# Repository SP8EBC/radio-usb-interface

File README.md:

# An USB interface between PC/RPi/ThinClient and any Land Mobile 2way Radio
Features:
1. Single USB connection to the PC.
2. Integrated USB 2.0 hub.
3. Integrated USB audio codec IC (Texas Instruments PCM2900) detected as a regular sound card.
4. Integrated double USB-UART controller (ftdi FT2232H) to control PTT and CarrierSense/COR/ChannelBusy lines.
5. Ground Separated RS232 for communication with the radio using CAT/IV-C or simmilar protocol
6. Ground Separated audio lines
7. Spare 2 USB ports exposed from the hub for connecting external devices.

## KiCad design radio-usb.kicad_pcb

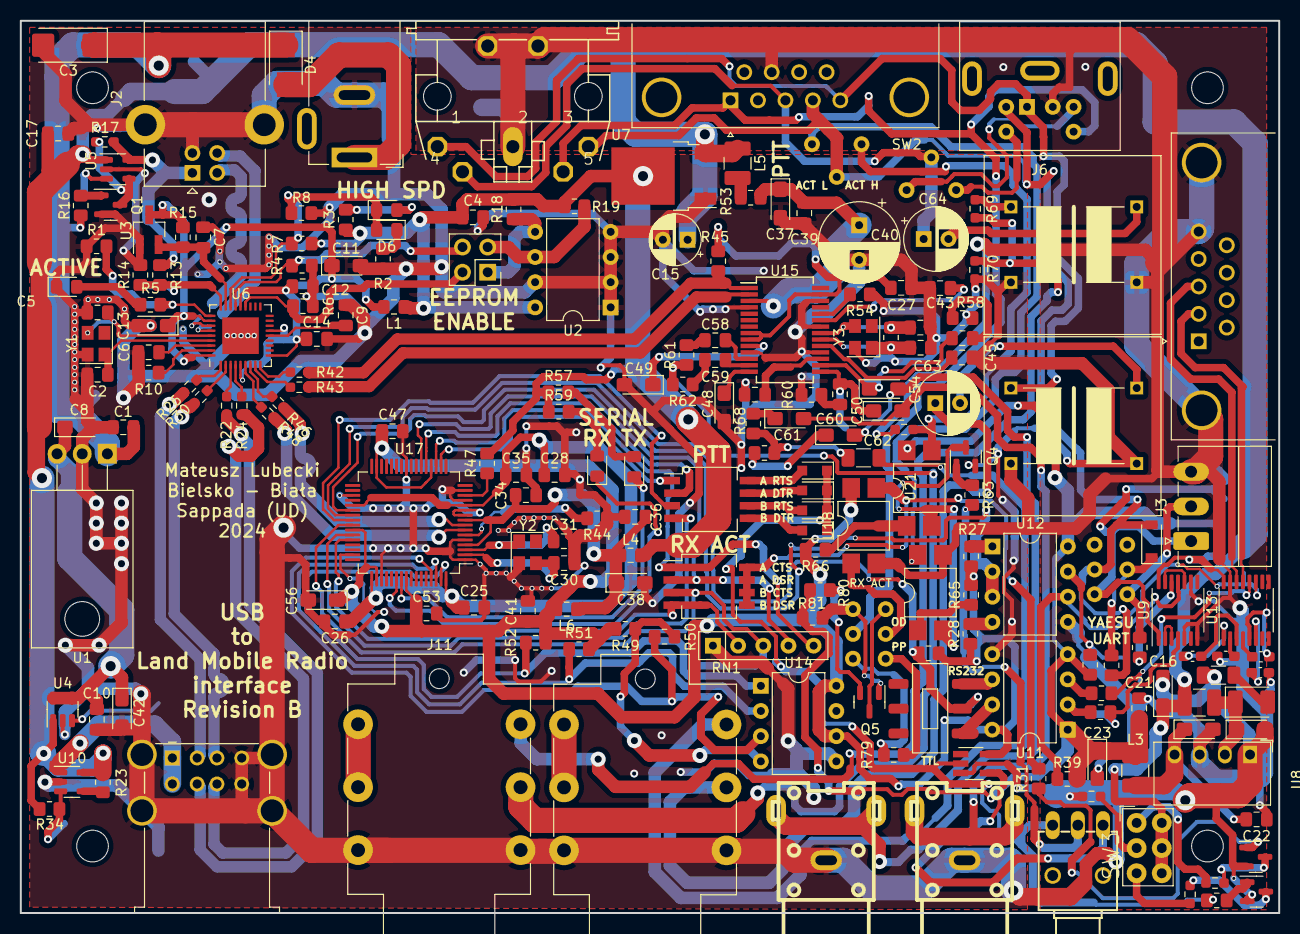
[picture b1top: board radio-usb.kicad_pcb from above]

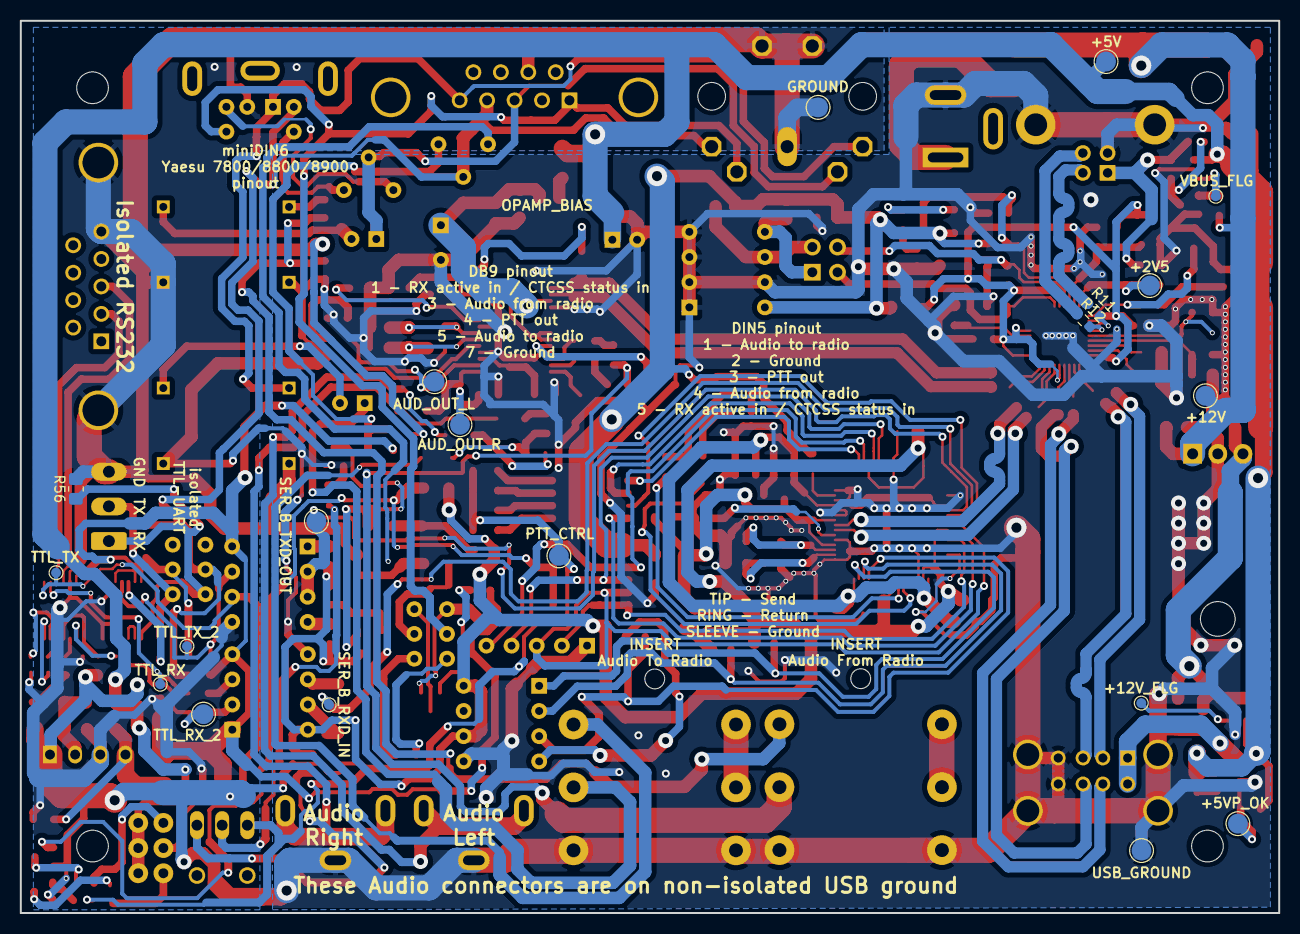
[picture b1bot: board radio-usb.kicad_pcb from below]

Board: 2 copper layers, 127.0 x 90.0 mm, 225 parts (20 on the bottom side), 171 nets.

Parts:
C1, C4, C7, C10, C12, C14, C17, C21, C22, C25, C26, C34, C35, C36, C39, C41, C47, C53: 100n; C_0805_2012Metric_Pad1.18x1.45mm_HandSolder
C2, C5, C30, C31, C51, C52: 18p; C_0805_2012Metric_Pad1.18x1.45mm_HandSolder
C3: 10u; CP_EIA-6032-28_Kemet-C_Pad2.25x2.35mm_HandSolder
C6, C9, C27, C43, C45, C46: 1u; C_0805_2012Metric_Pad1.18x1.45mm_HandSolder
C8, C11, C13, C37, C38, C48, C49, C50, C54, C56, C60, C61: 10u; CP_EIA-3216-18_Kemet-A_Pad1.58x1.35mm_HandSolder
C15: 100u; CP_Radial_D5.0mm_P2.50mm
C16, C18, C20, C23, C42: 22u; CP_EIA-3216-18_Kemet-A_Pad1.58x1.35mm_HandSolder
C19: 100u; CP_EIA-3528-21_Kemet-B_Pad1.50x2.35mm_HandSolder
C24, C29, C32, C33: 100n; C_0603_1608Metric_Pad1.08x0.95mm_HandSolder
C28: 3u3; C_0805_2012Metric_Pad1.18x1.45mm_HandSolder
C40: 470u; CP_Radial_D8.0mm_P3.50mm
C55, C57: 22n; C_0805_2012Metric_Pad1.18x1.45mm_HandSolder
C58, C59: 4u7; C_0805_2012Metric_Pad1.18x1.45mm_HandSolder
C62: 10u; C_1206_3216Metric_Pad1.33x1.80mm_HandSolder
C63, C64: 220u; CP_Radial_D6.3mm_P2.50mm
D1: LED_ACTIVE; LED_0805_2012Metric_Pad1.15x1.40mm_HandSolder
D4: B130-13-F; D_SMA
D5: DNP; LED_0805_2012Metric_Pad1.15x1.40mm_HandSolder
D6: LED_HS; LED_0805_2012Metric_Pad1.15x1.40mm_HandSolder
D7: 1N4148W; D_SOD-123
D12: 1882.2781; LED_MENTOR_1882
D15, D16: LED; LED_0805_2012Metric_Pad1.15x1.40mm_HandSolder
D17, D18, D19, D20: RB751V40T1G; D_SOD-323_HandSoldering
H1, H2, H3, H4: MountingHole; MountingHole_3.2mm_M3
J1: Barrel_Jack; BarrelJack_GCT_DCJ200-10-A_Horizontal
J2: miniUSB; USB_B_Lumberg_2411_02_Horizontal
J3: 15EDGRC-3.5-03P-14; PhoenixContact_MC_1,5_3-G-3.5_1x03_P3.50mm_Horizontal
J4: DB9_Female; DSUB-9_Female_Horizontal_P2.77x2.84mm_EdgePinOffset4.94mm_H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
J5: EEP_EN; PinHeader_2x02_P2.54mm_Vertical
J6: Mini-DIN-6; Mini-DIN_Female_TM0508A
J7: EDAC 690-008-221-904; USB_A_Wuerth_61400826021_Horizontal_Stacked
J8: DB9_Male; DSUB-9_Male_Horizontal_P2.77x2.84mm_EdgePinOffset4.94mm_Hou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
J9, J10: Conn_Coaxial; rca_cliff_F68371
J11, J12: ACJS-MHDRM; Jack_6.35mm_ACJS-MHDRM
L1, L4, L6: 1u; L_0805_2012Metric_Pad1.15x1.40mm_HandSolder
L2, L3, L5: 4u7; L_1210_3225Metric_Pad1.42x2.65mm_HandSolder
Q1, Q2, Q3, Q4: BC846C; SOT-23
Q5: BC856; SOT-23
R1, R3, R7: DNP; R_0805_2012Metric_Pad1.20x1.40mm_HandSolder
R2, R5, R57, R59: 620; R_0805_2012Metric_Pad1.20x1.40mm_HandSolder
R4, R6, R8, R13, R14, R15: 100k; R_0805_2012Metric_Pad1.20x1.40mm_HandSolder
R9: 4k7; R_0805_2012Metric_Pad1.20x1.40mm_HandSolder
R10, R44: 12k; R_0805_2012Metric_Pad1.20x1.40mm_HandSolder
R11, R12, R42, R43, R46, R48: 22; R_0603_1608Metric_Pad0.98x0.95mm_HandSolder
R16, R18, R19, R23, R38, R39, R49, R51, R52, R61, R62, R67, R68: 10k; R_0805_2012Metric_Pad1.20x1.40mm_HandSolder
R17, R78: 10k; R_0603_1608Metric_Pad0.98x0.95mm_HandSolder
R20: 0R68; R_1206_3216Metric_Pad1.30x1.75mm_HandSolder
R22, R24, R26, R30: 33; R_0603_1608Metric_Pad0.98x0.95mm_HandSolder
R27, R28, R32, R33, R79, R80: 680; R_0805_2012Metric_Pad1.20x1.40mm_HandSolder
R29, R31, R40, R41, R50, R56, R63: 2k2; R_0805_2012Metric_Pad1.20x1.40mm_HandSolder
R34: R_Small; R_0805_2012Metric_Pad1.20x1.40mm_HandSolder
R35, R36, R37: 620; R_0603_1608Metric_Pad0.98x0.95mm_HandSolder
R45: 1k5; R_0805_2012Metric_Pad1.20x1.40mm_HandSolder
R47: 1k; R_0805_2012Metric_Pad1.20x1.40mm_HandSolder
R53: 2R2; R_0805_2012Metric_Pad1.20x1.40mm_HandSolder
R54: 0; R_0805_2012Metric_Pad1.20x1.40mm_HandSolder
R55: 1M; R_0805_2012Metric_Pad1.20x1.40mm_HandSolder
R58, R60: 16R; R_0805_2012Metric_Pad1.20x1.40mm_HandSolder
R65, R66: 330; R_0805_2012Metric_Pad1.20x1.40mm_HandSolder
R69: 0; R_0603_1608Metric_Pad0.98x0.95mm_HandSolder
R70: DNP; R_0603_1608Metric_Pad0.98x0.95mm_HandSolder
R81: 22k; R_0805_2012Metric_Pad1.20x1.40mm_HandSolder
RN1: 10k; R_Array_SIP5
SW1: SW_Push_DPDT; Alps_SSSS222700
SW2, SW7: SW_SPDT; Alps_SSSS213000
SW3: SW_SPDT; TL3XWO
SW4, SW5: A6H-4101; SW_DIP_SPSTx04_Slide_Copal_CHS-04B_W7.62mm_P1.27mm
SW6: SW_DPDT_x2; Alps_SSSS222700
SW8: SW_SPDT; Ninigi_MSS-2235S
TP1: +12V_FLG; TestPoint_Pad_D1.0mm
TP2: VB_FLG; TestPoint_Pad_D1.0mm
TP3: +5VP_OK; TestPoint_Pad_D2.0mm
TP4: TTL_TX; TestPoint_Pad_D1.0mm
TP5: TTL_RX; TestPoint_Pad_D1.0mm
TP6: TTL_TX_2; TestPoint_Pad_D1.0mm
TP7: TTL_RX_2; TestPoint_Pad_D2.0mm
TP8: SER_B_TXD_OUT; TestPoint_Pad_D2.0mm
TP9: SER_B_RXD_IN; TestPoint_Pad_D1.0mm
TP10: AUD_OUT_L; TestPoint_Pad_D2.0mm
TP11: AUD_OUT_R; TestPoint_Pad_D2.0mm
TP13: PTT_CTRL; TestPoint_Pad_D2.0mm
TP14: USB_GROUND; TestPoint_Pad_D2.0mm
TP15: GROUND; TestPoint_Pad_D2.0mm
TP16: +12V; TestPoint_Pad_D2.0mm
TP17: +2V5; TestPoint_Pad_D2.0mm
TP18: +5V; TestPoint_Pad_D2.0mm
U1: L7805; TO-220-3_Horizontal_TabDown
U2: 24LC04; DIP-8_W7.62mm
U3: APX809_810-xxSA; SOT-23_Handsoldering
U4, U5: AP22814AW5; SOT-23-5
U6: USB2514B-AEZC; QFN-36-1EP_6x6mm_P0.5mm_EP3.7x3.7mm
U7: LM1117-3.3; TO-252-2
U8: TBA 1-0511; Converter_DCDC_Murata_CRE1xxxxxx3C_THT
U9: 4069; TSSOP-14_4.4x5mm_P0.65mm
U10: AP2171W; SOT-23-5
U11, U12: TLP2662; DIP-8_W7.62mm
U13: MAX3232; TSSOP-16_4.4x5mm_P0.65mm
U14: AT93C46D; DIP-8_W7.62mm
U15: PCM2900CDB; SSOP-28_5.3x10.2mm_P0.65mm
U16: 74AHCT1G04; SOT-23-5_HandSoldering
U17: FT2232HL; LQFP-64_10x10mm_P0.5mm
U18, U20, U21: PC817; SMDIP-4_W7.62mm
U19, U22: CRIYCHLEY9000; NORMAL
X1: MAB5SH
Y1: 24MHz; Crystal_SMD_Abracon_ABM8G-4Pin_3.2x2.5mm
Y2, Y3: 12MHz; Crystal_SMD_Abracon_ABM8G-4Pin_3.2x2.5mm

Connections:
+1V8: C25.1, C26.1, C28.1, C35.1, U17.12 (VCORE), U17.37 (VCORE), U17.49 (VREGOUT), U17.64 (VCORE)
+2V5: R13.2, R14.1, TP17.1, U6.27 (VBUS_DET)
+3V3: C4.1, L1.1, L4.1, R3.1, R7.1, R18.2, R19.2, R47.2, R57.1, R59.1, U2.8 (VCC), U7.2 (VO)
+5V: C15.1, C16.1, C17.1, D12.1 (AB), D12.3 (AR), D12.5 (AG), L2.1, L5.1, R23.2, R34.1, TP18.1, U4.1 (OUT), U5.1 (OUT), U7.3 (VI), U10.5 (IN)
+5VP: J7.1 (VBUS1), J7.5 (VBUS2), U10.1 (OUT)
+12V: C1.1, C3.1, D4.1 (K), R16.1, TP16.1, U1.1 (IN)
/5VD12: C8.1, C10.1, C42.1, U1.3 (OUT), U4.4 (EN), U4.5 (IN)
/+5VP_EN: R23.1, U10.4 (EN)
/+5VP_OK: R34.2, TP3.1, U10.3 (~FLG)
/AF_FRM_RADIO_PREINS: J11.T, R69.1, R70.2
/AUD_IN_LEFT: C58.1, U15.12 (VINL)
/AUD_IN_RIGHT: C59.1, U15.13 (VINR)
/AUD_IN_SUM: J11.R, R61.1, R62.2
/AUD_OUT_LEFT: C54.1, C55.2, TP10.1, U15.16 (VOUTL)
/AUD_OUT_RIGHT: C50.1, C57.2, TP11.1, U15.15 (VOUTR)
/AUD_OUT_SUM: C62.2, J12.T
/AUD_USB_DN: R43.2, U15.2 (D-)
/AUD_USB_DP: R42.2, R45.1, U15.1 (D+)
/AUD_VBUS: C37.1, C39.1, C40.1, R53.2, U15.3 (VBUS)
/AUD_VDDI: C27.1, R45.2, U15.8 (SEL0), U15.9 (SEL1), U15.27 (VDDI)
/CAT_UART_RX: J3.1, R56.1, SW1.6 (C), U9.1
/CAT_UART_TX: J3.2, R40.1, SW1.3 (C)
/D+: J2.3 (D+), R12.1
/D-: J2.2 (D-), R11.1
/DCDC_IN: C18.1, C19.1, L2.2, U8.2 (+VIN)
/DCDC_OUT: C20.1, C22.2, L3.1, U8.4 (+VOUT)
/DP1+: J7.3 (D1+), R30.2
/DP1-: J7.2 (D1-), R26.2
/DP2+: J7.7 (D2+), R24.2
/DP2-: J7.6 (D2-), R22.2
/H_AUD_USBD+: R42.1, U6.9 (USBDP_DN4/PRT_DIS_P4)
/H_AUD_USBD-: R43.1, U6.8 (USBDM_DN4/PRT_DIS_M4)
/H_BIAS: R10.2, U6.35 (RBIAS)
/H_DP1+: R30.1, U6.2 (USBDP_DN1/PRT_DIS_P1)
/H_DP1-: R26.1, U6.1 (USBDM_DN1/PRT_DIS_M1)
/H_DP2+: R24.1, U6.4 (USBDP_DN2/PRT_DIS_P2)
/H_DP2-: R22.1, U6.3 (USBDM_DN2/PRT_DIS_M2)
/H_EE_SCL: J5.3, R19.1, U2.6 (SCL)
/H_EE_SDA: J5.1, R18.1, U2.5 (SDA)
/H_HOST_USBD+: R12.2, U6.31 (USBDP_UP)
/H_HOST_USBD-: R11.2, U6.30 (USBDM_UP)
/H_REM0: R1.2, R5.2, U6.28 (SUSP_IND/LOCAL_PWR/NON_REM0)
/H_REM1: J5.2, R6.2, U6.22 (SDA/SMBDATA/NON_REM1)
/H_RST: C7.2, R15.2, U3.2 (~RST), U6.26 (RESET_N)
/H_SEL0: J5.4, R4.2, U6.24 (SCL/SMBCLK/CFG_SEL0)
/H_SEL1: D5.1 (K), D6.2 (A), R7.2, R8.2, U6.25 (HS_IND/CFG_SEL1)
/H_SER_USBD+: R46.1, U6.7 (USBDP_DN3/PRT_DIS_P3)
/H_SER_USBD-: R48.1, U6.6 (USBDM_DN3/PRT_DIS_M3)
/H_VDD: C11.1, C12.1, C13.1, C14.1, L1.2, R15.1, U3.3 (Vcc), U6.5 (VDDA33), U6.10 (VDDA33), U6.15 (VDD33), U6.23 (VDD33), U6.29 (VDDA33), U6.36 (VDDA33)
/H_XTALIN: C2.1, U6.33 (XTALIN/CLKIN), Y1.1
/H_XTALO: C5.1, U6.32 (XTALOUT), Y1.3
/PTT_ACTH: R78.1, SW7.3 (C), U21.3
/PTT_ACTL: SW7.1 (A), U20.4
/PTT_CTRL: D17.1 (K), D18.1 (K), D19.1 (K), D20.1 (K), R41.2, SW3.3 (C), TP13.1, U16.2
/PTT_CTRL_SW: Q4.1 (B), R63.1
/RCA_LEFT: C54.2, C60.2, J10.1 (In)
/RCA_RIGHT: C50.2, C61.2, J9.1 (In)
/RS232RX: J8.2, U13.13 (R1IN)
/RS232TX: J8.3, U13.14 (T1OUT)
/RX_ACT_SEP: R31.2, SW5.5, SW5.6, SW5.7, SW5.8, U18.3
/SER_A_CTS_IN: RN1.5 (R4), SW5.1, U17.19 (ADBUS3)
/SER_A_DSR_IN: RN1.4 (R3), SW5.2, U17.22 (ADBUS5)
/SER_A_DTR_OUT: SW4.2, U17.21 (ADBUS4)
/SER_A_RTS_OUT: SW4.1, U17.18 (ADBUS2)
/SER_B_CTS_IN: RN1.3 (R2), SW5.3, U17.41 (BDBUS3)
/SER_B_DSR_IN: RN1.2 (R1), SW5.4, U17.44 (BDBUS5)
/SER_B_DTR_OUT: SW4.4, U17.43 (BDBUS4)
/SER_B_RTS_OUT: SW4.3, U17.40 (BDBUS2)
/SER_B_RXD_IN: R29.1, SW8.2 (B), TP9.1, U17.39 (BDBUS1)
/SER_B_RXD_RS: SW8.3 (C), U11.6 (VO2)
/SER_B_RXD_TTL: SW8.1 (A), U11.7 (VO1)
/SER_B_RXLED: D16.1 (K), U17.54 (BCBUS3)
/SER_B_TXD_OUT: TP8.1, U12.2 (C1), U12.3 (C2), U17.38 (BDBUS0)
/SER_B_TXLED: D15.1 (K), U17.55 (BCBUS4)
/SER_D+: R46.2, U17.8 (DP)
/SER_D-: R48.2, U17.7 (DM)
/SER_EECS: R52.1, U14.1 (CS), U17.63 (EECS)
/SER_EEDT: R50.1, U14.3 (DI), U17.61 (EEDATA)
/SER_VPLL: C34.1, C36.1, C38.1, L4.2, L6.1, U17.4 (VPHY), U17.9 (VPLL)
/SER_XI: C30.1, U17.2 (OSCI), Y2.3
/SER_XO: C31.1, U17.3 (OSCO), Y2.1
/TTL_RX: R33.2, TP5.1, U13.12 (R1OUT)
/TTL_RX_2: R32.2, TP7.1, U9.4
/TTL_TX: R39.1, TP4.1, U12.6 (VO2), U13.11 (T1IN)
/TTL_TX_2: R38.1, TP6.1, U9.11, U12.7 (VO1)
/YAESU_FILTERED_AUD: J6.5, SW2.1 (A)
/YAESU_FLAT_AUD: J6.4, SW2.3 (C)
/~PTT_CTRL: SW3.1 (A), U16.4
/~SER_RST: R47.1, U17.14 (~RESET)
AF_FRM_RADIO: C64.1, J4.3, SW2.2 (B), X1.4
AF_TO_RADIO: J4.5, J6.1, U19.P$1, X1.1
GND: C1.2, C2.2, C3.2, C4.2, C5.2, C6.1, C7.1, C8.2, C9.1, C10.2, C11.2, C12.2, C13.2, C14.2, C15.2, C16.2, C17.2, C18.2, C25.2, C26.2, C27.2, C28.2, C30.2, C31.2, C34.2, C35.2, C36.2, C37.2, C38.2, C39.2, C40.2, C41.2, C42.2, C43.2, C45.2, C46.2, C47.2, C48.2, C49.2, C51.2, C52.2, C53.2, C56.2, D1.1 (K), J1.2, J2.4 (GND), J2.5 (Shield), J7.4 (GND1), J7.8 (GND2), J7.9 (Shield), J9.2 (Ext), J10.2 (Ext), J11.S, J11.SN, J12.S, J12.SN, Q1.2 (E), Q2.2 (E), Q3.2 (E), Q4.2 (E), R1.1, R2.1, R4.1, R6.1, R8.1, R10.1, R14.2, R20.1, R35.2, R44.1, R54.1, R58.1, R60.1, R70.1, RN1.1 (common), TP14.1, U1.2 (GND), U2.1 (A0), U2.2 (A1), U2.3 (A2), U2.4 (GND), U2.7 (WP), U3.1 (GND), U4.2 (GND), U5.2 (GND), U6.37 (VSS), U7.1 (GND), U8.1 (-VIN), U10.2 (GND), U11.5 (GND), U14.5 (GND), U15.4 (DGNDU), U15.11 (AGNDC), U15.18 (AGNDP), U15.22 (AGNDX), U15.26 (DGND), U16.3 (GND), U17.1 (GND), U17.5 (GND), U17.10 (AGND), U17.11 (GND), U17.13 (TEST), U17.15 (GND), U17.25 (GND), U17.35 (GND), U17.47 (GND), U17.51 (GND), U19.P$4, U22.P$2, Y1.4, Y2.2, Y3.4
GNDREF: C20.2, C21.2, C22.1, C23.2, C32.2, C33.2, J3.3, J4.7, J6.2, J8.0 (PAD), J8.5, R56.2, R78.2, TP15.1, U8.3 (-VOUT), U9.5, U9.7 (VSS), U9.9, U12.5 (GND), U13.15 (GND), U18.2, U19.P$2, U20.3, U22.P$4, X1.2, X1.PE, X1.PE@ (PE)
unnamed: C6.2, U6.34 (PLLFILT)
unnamed: C9.2, U6.14 (CRFILT)
unnamed: C19.2, R20.2
unnamed: C24.1, U13.1 (C1+)
unnamed: C24.2, U13.3 (C1-)
unnamed: C29.1, U13.4 (C2+)
unnamed: C29.2, U13.5 (C2-)
unnamed: C32.1, U13.2 (VS+)
unnamed: C33.1, U13.6 (VS-)
unnamed: C43.1, U15.23 (VCCXI)
unnamed: C45.1, U15.19 (VCCP2I)
unnamed: C46.1, U15.17 (VCCP1I)
unnamed: C48.1, U15.14 (VCOM)
unnamed: C49.1, U15.10 (VCCCI)
unnamed: C51.1, R55.2, U15.21 (XTI), Y3.3
unnamed: C52.1, R55.1, U15.20 (XTO), Y3.1
unnamed: C55.1, R58.2
unnamed: C57.1, R60.2
unnamed: C58.2, R61.2
unnamed: C59.2, R62.1
unnamed: C60.1, R67.1
unnamed: C61.1, R68.1
unnamed: C62.1, R67.2, R68.2
unnamed: C63.1, J12.R
unnamed: C63.2, U19.P$3
unnamed: C64.2, U22.P$3
unnamed: D1.2 (A), R5.1
unnamed: D4.2 (A), J1.1
unnamed: D5.2 (A), R3.2
unnamed: D6.1 (K), R2.2
unnamed: D7.1 (K), R9.1, SW1.2 (B)
unnamed: D12.2 (KB), R37.1
unnamed: D12.4 (KR), R35.1
unnamed: D12.6 (KR), R36.1
unnamed: D15.2 (A), R57.2
unnamed: D16.2 (A), R59.2
unnamed: D17.2 (A), SW4.8
unnamed: D18.2 (A), SW4.7
unnamed: D19.2 (A), SW4.6
unnamed: D20.2 (A), SW4.5
unnamed: J11.RN, J11.TN
unnamed: J12.RN, J12.TN
unnamed: L5.2, R53.1
unnamed: Q1.1 (B), R16.2
unnamed: Q1.3 (C), R17.1, U5.4 (EN)
unnamed: Q2.1 (B), R31.1
unnamed: Q2.3 (C), R37.2
unnamed: Q3.1 (B), R41.1
unnamed: Q3.3 (C), R36.2
unnamed: Q4.3 (C), U20.2, U21.2
unnamed: Q5.1 (B), R81.1, SW6.4 (A)
unnamed: Q5.2 (E), R80.1
unnamed: Q5.3 (C), SW6.1 (A)
unnamed: R27.2, U12.1 (A1)
unnamed: R28.2, U12.4 (A2)
unnamed: R32.1, U11.2 (C1)
unnamed: R33.1, U11.3 (C2)
unnamed: R40.2, U9.12
unnamed: R44.2, U17.6 (REF)
unnamed: R49.1, R50.2, U14.4 (DO)
unnamed: R51.1, U14.2 (SCLK), U17.62 (EECLK)
unnamed: R54.2, U15.24 (DIN)
unnamed: R63.2, SW3.2 (B)
unnamed: R65.1, U20.1
unnamed: R66.1, U21.1
unnamed: R69.2, U22.P$1
unnamed: R79.1, SW6.6 (C)
unnamed: R79.2, SW6.3 (C)
unnamed: SW6.2 (B), U18.1
unnamed: TP1.1, U4.3 (~FLG)
unnamed: TP2.1, U5.3 (~FLG)
unnamed: U9.2, U9.3
unnamed: U9.10, U9.13
PTT: D7.2 (A), J4.4, J6.3, R9.2, SW1.5 (B), SW7.2 (B), X1.3
RX_ACTIVE: J4.1, J6.6, SW6.5 (B), X1.5
VBUS: J2.1 (VBUS), R13.1, R17.2, U5.5 (IN)
VCC: C41.1, C47.1, C53.1, C56.1, L6.2, R27.1, R28.1, R29.2, R49.2, R51.2, R52.2, R65.2, R66.2, U11.8 (VCC), U14.6 (ORG), U14.8 (VCC), U16.5 (VCC), U17.20 (VCCIO), U17.31 (VCCIO), U17.42 (VCCIO), U17.50 (VREGIN), U17.56 (VCCIO), U18.4
VD: C21.1, C23.1, L3.2, R38.2, R39.2, R80.2, R81.2, U9.14 (VDD), U11.1 (A1), U11.4 (A2), U12.8 (VCC), U13.16 (VCC), U21.4

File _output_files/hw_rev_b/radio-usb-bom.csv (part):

Reference, Quantity, Value, Footprint, Datasheet, DESCRIPTION
C1 C4 C7 C10 C12 C14 C17 C21 C22 C25 C26 C34 C35 C36 C39 C41 C47 C53 ,18,"100n","Capacitor_SMD:C_0805_2012Metric_Pad1.18x1.45mm_HandSolder","","08051C104KAT2A KYOCERA AVX"
C15 ,1,"100u","Capacitor_THT:CP_Radial_D5.0mm_P2.50mm","https://www.tme.eu/Document/4bbe885c35326128adf3c0aebd83337c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","UBT1H101MPD8 NICHICON"
C16 C18 C20 C23 C42 ,5,"22u","Capacitor_Tantalum_SMD:CP_EIA-3216-18_Kemet-A_Pad1.58x1.35mm_HandSolder","","TPSA106K010R0900 KYOCERA AVX"
C19 ,1,"100u","Capacitor_Tantalum_SMD:CP_EIA-3528-21_Kemet-B_Pad1.50x2.35mm_HandSolder","","TPSA106K010R0900 KYOCERA AVX"
C2 C5 C30 C31 C51 C52 ,6,"18p","Capacitor_SMD:C_0805_2012Metric_Pad1.18x1.45mm_HandSolder","","08055A180JAT2A KYOCERA AVX"
C24 C29 C32 C33 ,4,"100n","Capacitor_SMD:C_0603_1608Metric_Pad1.08x0.95mm_HandSolder","","06033G104ZAT2A KYOCERA AVX"
C28 ,1,"3u3","Capacitor_SMD:C_0805_2012Metric_Pad1.18x1.45mm_HandSolder","","0805ZD335KAT2A KYOCERA AVX"
C3 ,1,"10u","Capacitor_Tantalum_SMD:CP_EIA-6032-28_Kemet-C_Pad2.25x2.35mm_HandSolder","","TPSA106K010R0900 KYOCERA AVX"
C40 ,1,"470u","Capacitor_THT:CP_Radial_D8.0mm_P3.50mm","","NICHICON UHE1A471MPD1TA "
C55 C57 ,2,"22n","Capacitor_SMD:C_0805_2012Metric_Pad1.18x1.45mm_HandSolder","","08051C223KAT2A KYOCERA AVX"
C58 C59 ,2,"4u7","Capacitor_SMD:C_0805_2012Metric_Pad1.18x1.45mm_HandSolder","","0805YC475KAT2A KYOCERA AVX"
C6 C9 C27 C43 C45 C46 ,6,"1u","Capacitor_SMD:C_0805_2012Metric_Pad1.18x1.45mm_HandSolder","","0805YC105KAT2A KYOCERA AVX"
C62 ,1,"10u","Capacitor_SMD:C_1206_3216Metric_Pad1.33x1.80mm_HandSolder","","CL31A106MAHNNNE SAMSUNG"
C63 C64 ,2,"220u","Capacitor_THT:CP_Radial_D6.3mm_P2.50mm","https://www.tme.eu/Document/4bbe885c35326128adf3c0aebd83337c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","EEUFR1C221 PANASONIC"
C8 C11 C13 C37 C38 C48 C49 C50 C54 C56 C60 C61 ,12,"10u","Capacitor_Tantalum_SMD:CP_EIA-3216-18_Kemet-A_Pad1.58x1.35mm_HandSolder","","TPSA106K010R0900 KYOCERA AVX"
D1 ,1,"LED_ACTIVE","LED_SMD:LED_0805_2012Metric_Pad1.15x1.40mm_HandSolder","","KPT-2012CGCK KINGBRIGHT ELECTRONIC"
D12 ,1,"1882.2781","LED:LED_MENTOR_1882","https://www.cree.com/led-components/media/documents/1397-QLS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","1882.2781 MENTOR"
D15 D16 ,2,"LED","LED_SMD:LED_0805_2012Metric_Pad1.15x1.40mm_HandSolder","","KP-2012SYCK KINGBRIGHT ELECTRONIC"
D17 D18 D19 D20 ,4,"RB751V40T1G","Diode_SMD:D_SOD-323_HandSoldering","https://www.tme.eu/Document/b77eb958f5d9ac56ef472a800d34775b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","RB751V40T1G ONSEMI"
D4 ,1,"B130-13-F","Diode_SMD:D_SMA","","B130-13-F DIODES INCORPORATED"
D5 D6 ,2,"LED_HS","LED_SMD:LED_0805_2012Metric_Pad1.15x1.40mm_HandSolder","","KPT-2012SURC KINGBRIGHT ELECTRONIC"
D7 ,1,"1N4148W","Diode_SMD:D_SOD-123","https://www.vishay.com/docs/85748/1n4148w.pdf","1N4148W-AQ DIOTEC SEMICONDUCTOR"
H1 H2 H3 H4 ,4,"MountingHole","MountingHole:MountingHole_3.2mm_M3",""
J1 ,1,"Barrel_Jack","Connector_BarrelJack:BarrelJack_GCT_DCJ200-10-A_Horizontal",""
J11 J12 ,2,"ACJS-MHDRM","AV:Jack_6.35mm_ACJS-MHDRM","","ACJS-MHDRM AMPHENOL"
J2 ,1,"miniUSB","Connector_USB:USB_B_Lumberg_2411_02_Horizontal"," ~","DS1099-WN0 CONNFLY"
J3 ,1,"15EDGRC-3.5-03P-14","Connector_Phoenix_MC:PhoenixContact_MC_1,5_3-G-3.5_1x03_P3.50mm_Horizontal","https://www.tme.eu/Document/c7e2facf434c6541c93efde757aaf5e6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"
J4 ,1,"DB9_Female","Connector_Dsub:DSUB-9_Female_Horizontal_P2.77x2.84mm_EdgePinOffset4.94mm_Housed_MountingHolesOffset7.48mm"," ~","DE09-SN-24 ADAM TECH"
J5 ,1,"EEP_EN","Connector_PinHeader_2.54mm:PinHeader_2x02_P2.54mm_Vertical",""
J6 ,1,"Mini-DIN-6","AV:Mini-DIN_Female_TM0508A","http://service.powerdynamics.com/ec/Catalog17/Section%2011.pdf","4850.2610 SCHURTER"
J7 ,1,"EDAC 690-008-221-904","Connector_USB:USB_A_Wuerth_61400826021_Horizontal_Stacked","https://www.tme.eu/Document/bc38f05e107515c145d033d39722883f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","EDAC 690-008-221-904"
J8 ,1,"DB9_Male","Connector_Dsub:DSUB-9_Male_Horizontal_P2.77x2.84mm_EdgePinOffset4.94mm_Housed_MountingHolesOffset7.48mm"," ~","DE09-PN-24 ADAM TECH"
J9 J10 ,2,"Conn_Coaxial","AV:rca_cliff_F68371"," ~"
L1 L4 L6 ,3,"1u","Inductor_SMD:L_0805_2012Metric_Pad1.15x1.40mm_HandSolder","","Viking NL05KTC1R0 "
L2 L3 L5 ,3,"4u7","Inductor_SMD:L_1210_3225Metric_Pad1.42x2.65mm_HandSolder","https://www.tme.eu/Document/11b7ed33a7ee93321756e8b8c8bd2191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","Viking NLV10MTC4R7"
Q1 Q2 Q3 Q4 ,4,"BC846C","Package_TO_SOT_SMD:SOT-23","https://assets.nexperia.com/documents/data-sheet/BC846_SER.pdf","BC846C-AQ DIOTEC SEMICONDUCTOR"
Q5 ,1,"BC856","Package_TO_SOT_SMD:SOT-23","https://www.onsemi.com/pub/Collateral/BC860-D.pdf","BC856B-AQ DIOTEC SEMICONDUCTOR"
R1 R4 R6 R8 R13 R14 R15 ,7,"100k","Resistor_SMD:R_0805_2012Metric_Pad1.20x1.40mm_HandSolder","","ERJ6ENF1002V PANASONIC"
R10 R44 ,2,"12k","Resistor_SMD:R_0805_2012Metric_Pad1.20x1.40mm_HandSolder","","ERJ6ENF1202V PANASONIC"
R11 R12 R42 R43 R46 R48 ,6,"22","Resistor_SMD:R_0603_1608Metric_Pad0.98x0.95mm_HandSolder","","ERJ3EKF22R0V PANASONIC"
R17 R78 ,2,"10k","Resistor_SMD:R_0603_1608Metric_Pad0.98x0.95mm_HandSolder","","ERJ3EKF1002V PANASONIC"
R2 R3 R5 R57 R59 ,5,"620","Resistor_SMD:R_0805_2012Metric_Pad1.20x1.40mm_HandSolder","","ERJ6GEYJ621V PANASONIC"
R20 ,1,"0R68","Resistor_SMD:R_1206_3216Metric_Pad1.30x1.75mm_HandSolder",""
R22 R24 R26 R30 ,4,"33","Resistor_SMD:R_0603_1608Metric_Pad0.98x0.95mm_HandSolder","","ERJ3EKF33R0V PANASONIC"
R27 R28 R32 R33 R79 R80 ,6,"680","Resistor_SMD:R_0805_2012Metric_Pad1.20x1.40mm_HandSolder","","ERA6AEB681V PANASONIC"
R29 R31 R40 R41 R50 R56 R63 ,7,"2k2","Resistor_SMD:R_0805_2012Metric_Pad1.20x1.40mm_HandSolder","","ERJ6ENF2201V PANASONIC"
R34 ,1,"R_Small","Resistor_SMD:R_0805_2012Metric_Pad1.20x1.40mm_HandSolder",""
R35 R36 R37 ,3,"620","Resistor_SMD:R_0603_1608Metric_Pad0.98x0.95mm_HandSolder","","ERJ3EKF6200V PANASONIC"
R45 ,1,"1k5","Resistor_SMD:R_0805_2012Metric_Pad1.20x1.40mm_HandSolder","","ERA6AEB152V PANASONIC"
R47 ,1,"1k","Resistor_SMD:R_0805_2012Metric_Pad1.20x1.40mm_HandSolder","","ERJ6ENF1001V PANASONIC"
R53 ,1,"2R2","Resistor_SMD:R_0805_2012Metric_Pad1.20x1.40mm_HandSolder","","ERJP06J2R2V PANASONIC"
R54 ,1,"0","Resistor_SMD:R_0805_2012Metric_Pad1.20x1.40mm_HandSolder","","ERJ6GEY0R00V PANASONIC"
R55 ,1,"1M","Resistor_SMD:R_0805_2012Metric_Pad1.20x1.40mm_HandSolder","","ERJ6ENF1004V PANASONIC"
R58 R60 ,2,"16R","Resistor_SMD:R_0805_2012Metric_Pad1.20x1.40mm_HandSolder","","0805S8F160JT5E ROYAL OHM"
R65 R66 ,2,"330","Resistor_SMD:R_0805_2012Metric_Pad1.20x1.40mm_HandSolder","","ERJ6ENF3300V PANASONIC"
R69 ,1,"0","Resistor_SMD:R_0603_1608Metric_Pad0.98x0.95mm_HandSolder","","ERJ3GEY0R00V PANASONIC"
R7 R16 R18 R19 R23 R38 R39 R49 R51 R52 R61 R62 R67 R68 ,14,"10k","Resistor_SMD:R_0805_2012Metric_Pad1.20x1.40mm_HandSolder","","ERJ6ENF1002V PANASONIC"
R70 ,1,"DNP","Resistor_SMD:R_0603_1608Metric_Pad0.98x0.95mm_HandSolder",""
R81 ,1,"22k","Resistor_SMD:R_0805_2012Metric_Pad1.20x1.40mm_HandSolder","","ERJ6ENF2202V PANASONIC"
R9 ,1,"4k7","Resistor_SMD:R_0805_2012Metric_Pad1.20x1.40mm_HandSolder","","ERJ6ENF4701V PANASONIC"
RN1 ,1,"10k","Resistor_THT:R_Array_SIP5","http://www.vishay.com/docs/31509/csc.pdf","RNLA05G0103B0E ROYAL OHM"
SW1 ,1,"SW_Push_DPDT","switches_spdt_dpdt:Alps_SSSS222700","https://www.tme.eu/Document/c62ad11cd91cb94020bc0a3c66211e45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","Alps SSSS222700"
SW2 SW7 ,2,"SW_SPDT","switches_spdt_dpdt:Alps_SSSS213000","https://www.tme.eu/Document/2a8ee3f094bc2d9567cff99b6818da87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","SSSS213000 ALPS"
SW3 ,1,"SW_SPDT","switches_spdt_dpdt:TL3XWO",""
SW4 SW5 ,2,"A6H-4101","Button_Switch_SMD:SW_DIP_SPSTx04_Slide_Copal_CHS-04B_W7.62mm_P1.27mm","","OMRON A6H-4101"
SW6 ,1,"SW_DPDT_x2","switches_spdt_dpdt:Alps_SSSS222700","https://www.tme.eu/Document/c62ad11cd91cb94020bc0a3c66211e45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","ALPS SSSS222700"
SW8 ,1,"SW_SPDT","switches_spdt_dpdt:Ninigi_MSS-2235S","https://www.tme.eu/Document/2a8ee3f094bc2d9567cff99b6818da87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","SSSS213000 ALPS"
TP1 ,1,"+12V_FLG","TestPoint:TestPoint_Pad_D1.0mm",""
TP10 ,1,"AUD_OUT_L","TestPoint:TestPoint_Pad_D2.0mm",""
TP11 ,1,"AUD_OUT_R","TestPoint:TestPoint_Pad_D2.0mm",""
TP13 ,1,"PTT_CTRL","TestPoint:TestPoint_Pad_D2.0mm",""
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
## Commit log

2024-02-13 gitignore and removed unwanted backup files
2024-02-17 eagle library
2024-02-21 daily
2024-02-24 schematic ready
2024-02-25 routing usb differential pairs
2024-02-26 routing serial ftdi controller
2024-02-28 everything but audio codec
2024-02-29 some components around audio codec
2024-03-03 all components placed
2024-03-03 schematic export
2024-03-04 some pcb routing around io
2024-03-05 more pcb traces routing
2024-03-06 almost everything routed
2024-03-06 everything but ground poluygon and fixed bourns trafo pinout
2024-03-07 everything routed, bourns audio transformer footprint correcred, ground polygons
2024-03-08 silkscreen description and test points
2024-03-10 fixed mini din 6 orientation, fix via size problems
2024-03-10 new gitignore
2024-03-10 gerber files and another fabrication output
2024-03-12 updated bom and exported schematic, corrected some component values
2024-03-21 gerber exports and another files sent to PCBway for production
2024-04-06 fix with Y1 part number, cleanup in output files
2024-06-21 more cleanup
2024-06-25 hardware revision b schematic
2024-07-02 hw revision b done
2024-08-04 hardware revision b build
2024-08-19 final production files
2025-03-05 exported schematic
